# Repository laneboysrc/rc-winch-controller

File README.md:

rc-winch-controller
===================

This project is for a winch controller for Radio Controlled cars that uses channel 3 to operate the winch remotely.

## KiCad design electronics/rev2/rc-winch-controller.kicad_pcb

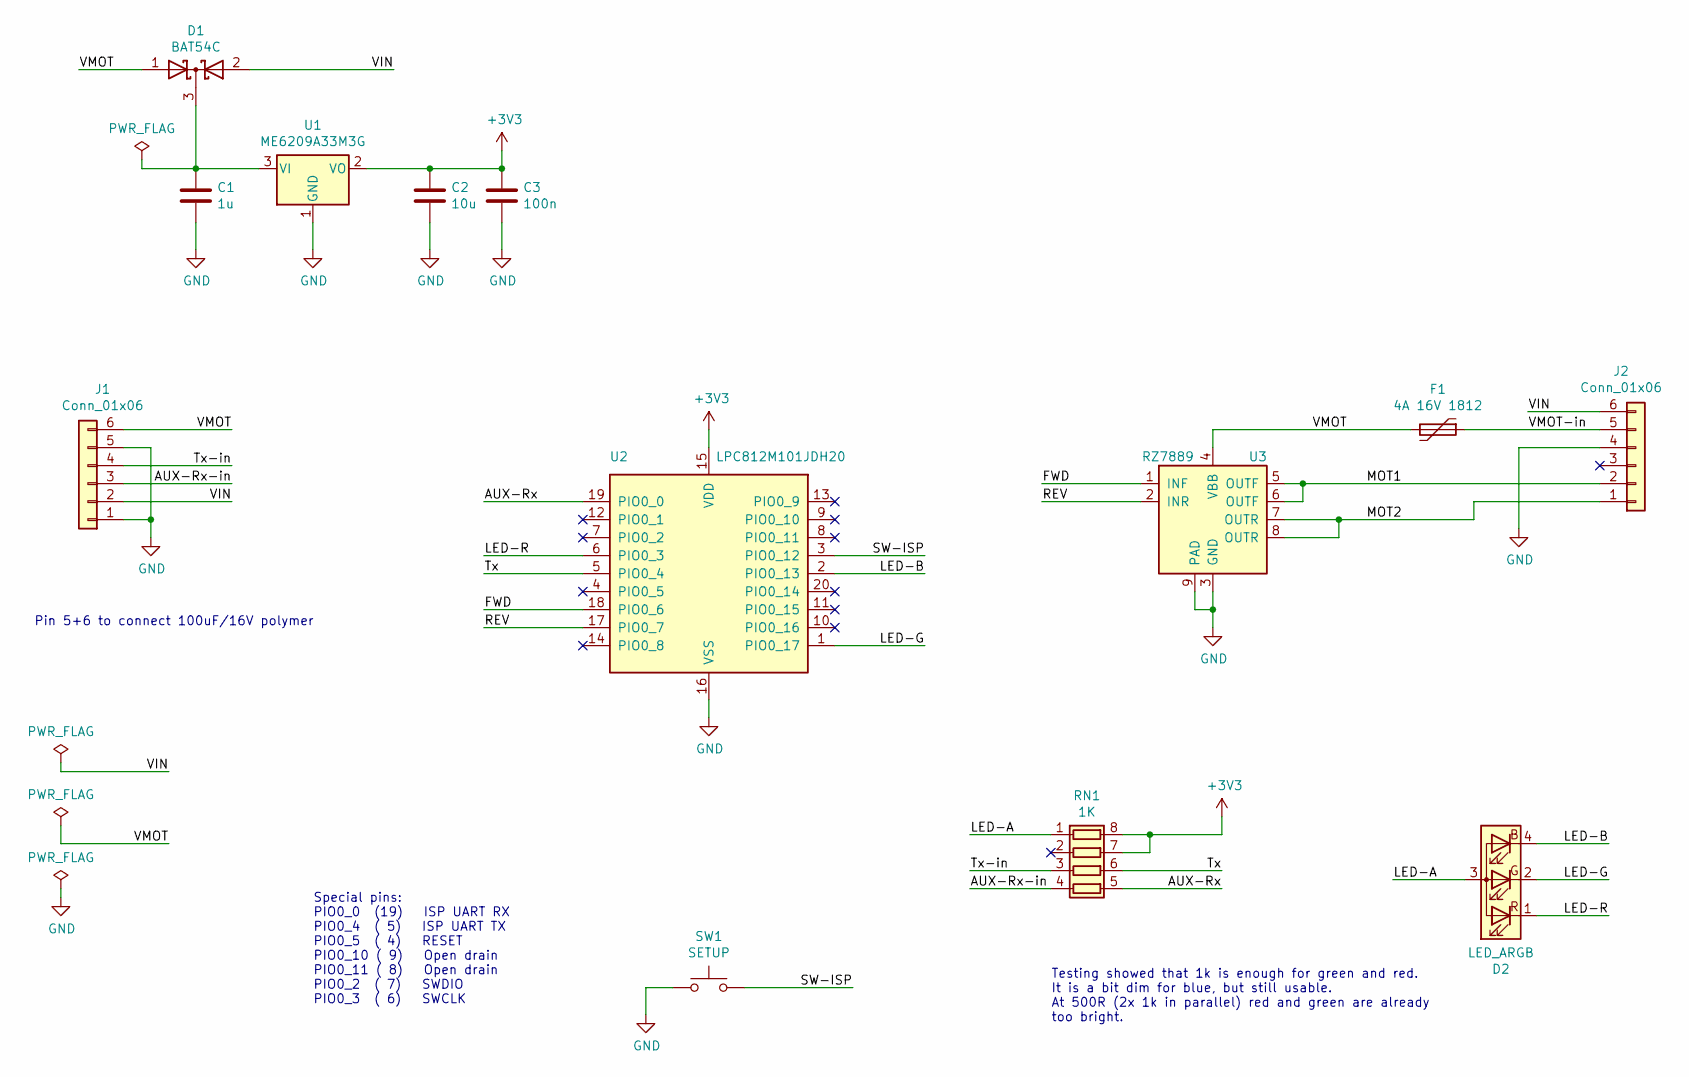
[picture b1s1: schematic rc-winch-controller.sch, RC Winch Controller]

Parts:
C1: 1u; C_0805_2012Metric
C2: 10u; C_0805_2012Metric
C3: 100n; C_0603_1608Metric
D1: BAT54C; SOT-23
D2: LED_ARGB; LED_RGB_XINGLIGHT_XL-2012RGBC
F1: 4A 16V 1812; Fuse_1812_4532Metric_Pad1.30x3.40mm_HandSolder
J1, J2: Conn_01x06; PinHeader_1x06_P2.54mm_Flat
RN1: 1K; R_Array_Convex_4x0603
SW1: SETUP; Tact switch 6x4x3
U1: ME6209A33M3G; SOT-23W
U2: LPC812M101JDH20; TSSOP-20_4.4x6.5mm_P0.65mm
U3: RZ7889; SOIC-8-1EP_3.9x4.9mm_P1.27mm_EP2.29x3mm_ThermalVias

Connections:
+3V3: C2.1, C3.1, RN1.7 (R2.2), RN1.8 (R1.2), U1.2 (VO), U2.15 (VDD)
/AUX-Rx: RN1.5 (R4.2), U2.19 (PIO0_0)
/AUX-Rx-in: J1.3, RN1.4 (R4.1)
/FWD: U2.18 (PIO0_6), U3.1 (INF)
/LED-A: D2.3 (A), RN1.1 (R1.1)
/LED-B: D2.4 (BK), U2.2 (PIO0_13)
/LED-G: D2.2 (GK), U2.1 (PIO0_17)
/LED-R: D2.1 (RK), U2.6 (PIO0_3)
/MOT1: J2.2, U3.5 (OUTF), U3.6 (OUTF)
/MOT2: J2.1, U3.7 (OUTR), U3.8 (OUTR)
/REV: U2.17 (PIO0_7), U3.2 (INR)
/SW-ISP: SW1.2, U2.3 (PIO0_12)
/Tx: RN1.6 (R3.2), U2.5 (PIO0_4)
/Tx-in: J1.4, RN1.3 (R3.1)
/VIN: D1.2 (A), J1.2, J2.6
/VMOT: D1.1 (A), F1.2, J1.6, U3.4 (VBB)
/VMOT-in: F1.1, J2.5
GND: C1.2, C2.2, C3.2, J1.1, J1.5, J2.4, SW1.1, U1.1 (GND), U2.16 (VSS), U3.3 (GND), U3.9 (PAD)
unnamed: C1.1, D1.3 (K), U1.3 (VI)

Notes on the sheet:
Special pins: PIO0_0 (19) ISP UART RX PIO0_4 ( 5) ISP UART TX PIO0_5 ( 4) RESET PIO0_10 ( 9) Open drain PIO0_11 ( 8) Open drain PIO0_2 ( 7) SWDIO PIO0_3 ( 6) SWCLK
Testing showed that 1k is enough for green and red. It is a bit dim for blue, but still usable. At 500R (2x 1k in parallel) red and green are already too bright.
Pin 5+6 to connect 100uF/16V polymer

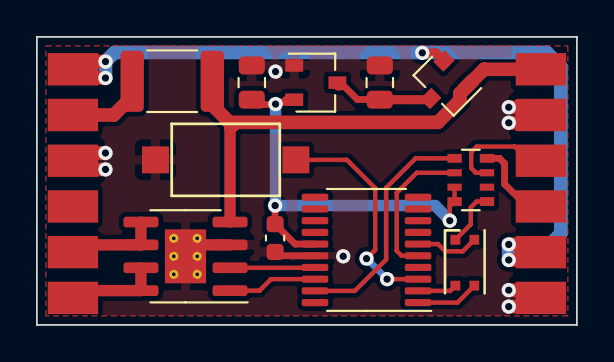
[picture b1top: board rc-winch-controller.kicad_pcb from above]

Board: 2 copper layers, 30.0 x 16.0 mm, 13 parts (0 on the bottom side), 19 nets.

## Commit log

2013-05-17 Add .gitignore
2013-05-17 Add license and readme file
2013-05-17 Add schematics and libraries Eagle
2013-05-17 Add library for PIC12F1840
2013-05-20 Continue working on the schematic
2013-05-20 Start on the board layout
2013-05-20 Add OSH Park design rules and CAM file
2013-05-20 Modify board vias
2013-05-20 Fix schemtic for P-channel FET being reversed
2013-05-21 Update MOSFET to include both drain pins
2013-05-21 Add jumper resistor to be able to switch between receiver power and external power
2013-05-21 Finalize board layout
2013-06-11 Remove tPlace and bPlace from CAM file to remove annoying markers for connectors
2013-06-11 Improve the board layout
2013-06-11 Add markers for IC pin 1 and fix silkscreen hitting solder mask
2013-06-11 Add bottom silk screen
2013-07-04 Add skeleton for firmware using SDCC
2013-07-04 Remove ASM files, they are generated by the compiler
2013-07-04 Added asm files to clean list
2013-07-04 Add compiler files to ignore list
2013-07-04 Start implementation of the winch controller, uart reader
2013-07-04 Add more code
2013-07-05 Use sdcc for linking instead of gplink directly
2013-07-05 Layout and Gerber for version sent to OSHPark
2013-07-05 Make local functions static for compiler optimization
2013-07-05 Add comments regarding PORT usage
2013-07-08 Add rudimentary motor code
2013-07-15 Add some thoughts regarding making of music with the motor.
2013-07-16 Add test code using compare mode on TIMER1 to toggle RA2 with 440 Hz
2013-07-23 Start implementing note tables
2013-07-24 Update documentation
2013-07-24 Further cleanup of defines and documentation
2013-07-24 Added Play_song functionality. Not tested yet.
2013-07-24 Add UART error handling
2013-07-24 Finalize implementation of the core logic
2013-07-24 Make startup sound only after valid command has been received.
2013-07-24 Remove pause from end of songs
2013-08-19 Use MOTOR macros instead of direct ports for song playing
2013-09-04 Make motor sound by running the motor forward and backwards instead of off and on
2013-09-04 Remove setting of wrong port to input
2013-09-05 Wait for 3 commands before initializing the winch.
    This ensures that we don't immediately draw a lot of current
    at start-up
2013-09-09 Start working on the servo input
    Just copied ASM code from the light controller.
2013-09-09 Add build rules for servo version of the winch controller
2013-09-09 Implement servo reading and normalization, incl. hysteresis
2013-09-10 Add documentation
2013-09-10 Full implementation ready, but not tested yet.
    Documentation updated.
2013-09-10 Fix servo input, not it is working fine.
2013-09-13 Update documentation in preperation for blog and YT video
2013-09-13 Add HEX file for distribution
2013-09-15 Use MIT license
2013-09-15 Update README with YT video
2013-09-15 Try again with YT embedding...
2015-05-14 Add modified controller for 3-Racing winch.
2015-05-15 Add program command
2015-05-15 Bugfix after testing, now fully working
2017-07-12 Add PDF version of the schematics
2017-07-12 Add dedicated BOM file and add capacitor voltage requirement
2017-07-25 Add pk2cmd for flashing the firmware
2017-08-14 Fix MOSFET shoot-through and ignore commands not meant for the winch
2018-03-30 Fix license file
2018-04-29 Make servo input work again
    Was broken when we changed the UART commands ...
2021-01-24 Start on Rev2 PCB
2021-01-25 Update PCB
2021-01-30 Update 3D models
2021-01-31 Update layout and silkscreen
2021-01-31 Tweak placement, layout and silk screen
2021-02-11 Change MCU to TSSOP 20 version
2021-02-12 Fix LED footprint and current limiting resistor
    1k is enough for red and green.
    It is a bit dark for blue, but 500R is too bright
    for red and green.
2021-02-14 Improve layout
2021-05-25 Remove YouTube video
